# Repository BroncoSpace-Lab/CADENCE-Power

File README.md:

This repository contains the development of the Solar and Battery Management system Boards that will be used for the CADENCE mission.

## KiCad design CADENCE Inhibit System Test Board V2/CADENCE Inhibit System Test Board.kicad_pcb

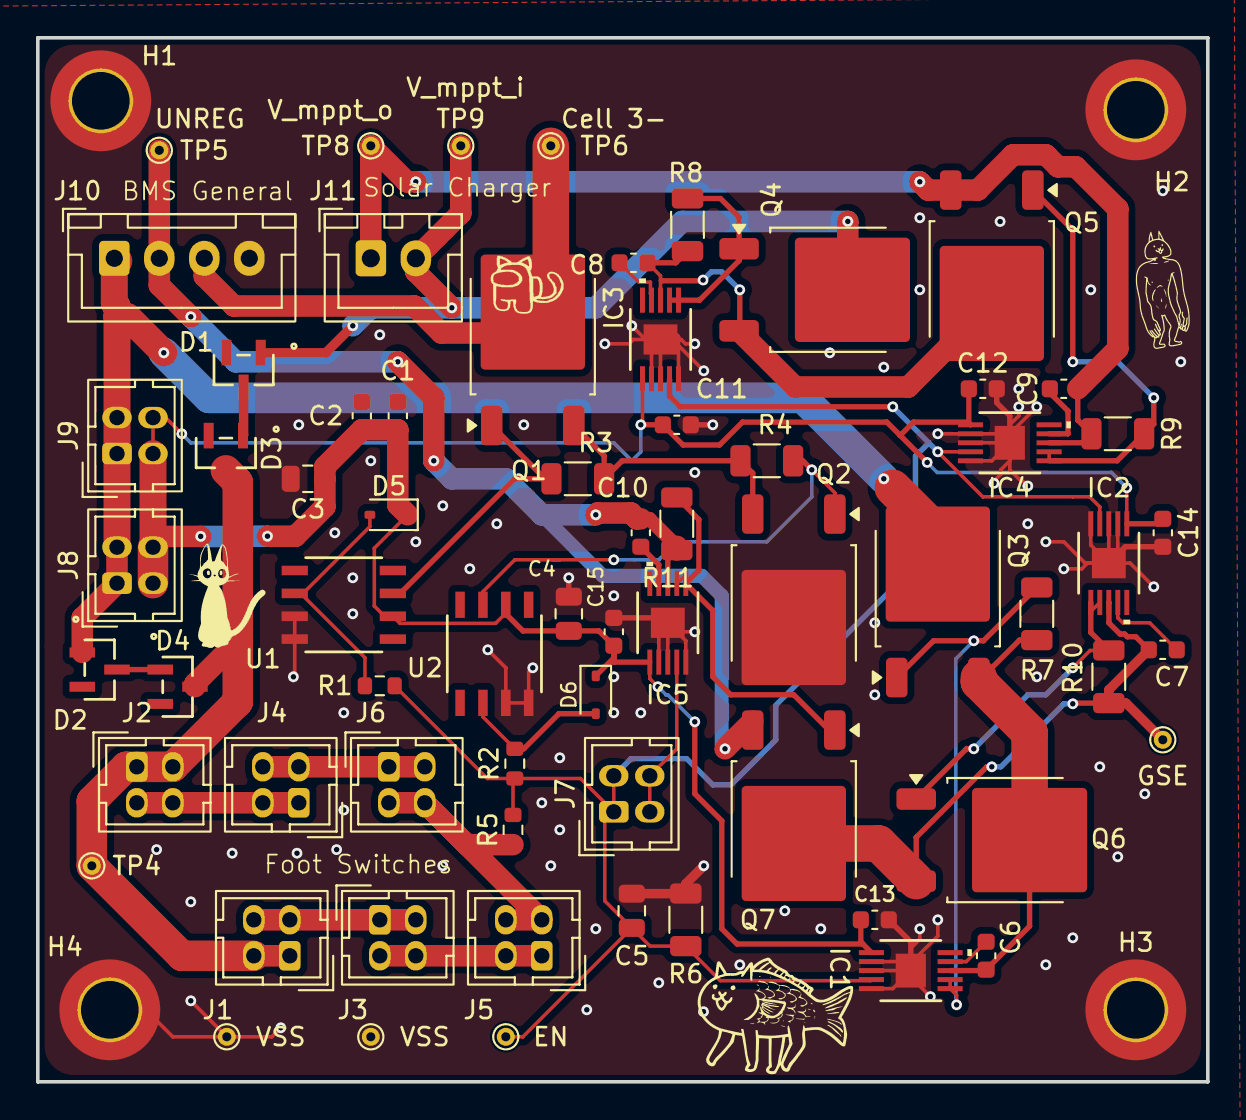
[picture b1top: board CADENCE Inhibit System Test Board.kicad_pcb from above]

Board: 2 copper layers, 65.0 x 58.0 mm, 70 parts (0 on the bottom side), 35 nets.

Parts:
C1, C2, C6, C7, C8, C9, C10, C11, C12, C13, C14, C15: 100nF; C_0603_1608Metric
C3, C4: 4.7uF; C_0805_2012Metric
C5: 10nF; C_0805_2012Metric
D1, D2, D3, D4: MMBD914LT1G; SOT-23_ONS
D5, D6: 1N5711WS-7-F; D_SOD-323
GSE: GSE; TestPoint_THTPad_D1.0mm_Drill0.5mm
H1, H2, H3, H4: MountingHole_Pad; MountingHole_3.2mm_M3_DIN965_Pad_TopOnly
IC1, IC2, IC3, IC4, IC5: LTC7004IMSE#WTRPBF; MSE_05-08-1664_ADI
J1, J2, J3, J4, J5, J6, J7, J8, J9: INHIBIT_P2; Hirose_DF11-4DP-2DSA_2x02_P2.00mm_Vertical
J10: Conn_01x04; JST_XH_B4B-XH-A_1x04_P2.50mm_Vertical
J11: Conn_01x02; JST_XH_B2B-XH-A_1x02_P2.50mm_Vertical
Q1, Q2, Q3, Q4, Q5, Q6, Q7: SUD23N06-31-GE3; TO-252-2
R1, R2: 47k; R_0603_1608Metric
R3, R4, R6, R7, R8, R9, R10, R11: 100K; R_1206_3216Metric
R5: 39k; R_0603_1608Metric
TP1, TP7: VSS; TestPoint_THTPad_D1.0mm_Drill0.5mm
TP2: EN; TestPoint_THTPad_D1.0mm_Drill0.5mm
TP4: Voltage Level; TestPoint_THTPad_D1.0mm_Drill0.5mm
TP5: UNREG; TestPoint_THTPad_D1.0mm_Drill0.5mm
TP6: Cell 3-; TestPoint_THTPad_D1.0mm_Drill0.5mm
TP8: V_mppt_o; TestPoint_THTPad_D1.0mm_Drill0.5mm
TP9: V_mppt_i; TestPoint_THTPad_D1.0mm_Drill0.5mm
U1, U2: MIC4427YM-TR; SOIC-8_M_MCH

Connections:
Cell 1+: D2.1 (A), J8.1, J8.3, J9.1, J9.3, J10.1, Q3.2 (D)
Cell 3-: J10.3, Q1.2 (D), TP6.1 (1_1)
EN: C5.2, IC1.4 (INP), IC2.4 (INP), IC3.4 (INP), IC4.4 (INP), J7.1, J7.3, R1.1, R2.1, R5.2, R6.1, TP2.1 (1_1)
HIGH_SIDE_PWR: C1.1, C2.1, C3.1, C4.1, C11.1, C12.1, C13.1, C14.1, C15.1, D5.1 (K), D6.1 (K), IC1.1 (VCC), IC2.1 (VCC), IC3.1 (VCC), IC4.1 (VCC), IC5.1 (VCC), J8.2, J8.4, J9.2, J9.4, U1.6 (V_{S}), U2.6 (V_{S})
unnamed: D1.3 (K), D3.1 (A)
unnamed: D2.3 (K), D4.1 (A)
unnamed: D3.3 (K), D4.3 (K), J1.1, J1.3, J2.1, J2.3, TP4.1 (1_1)
unnamed: D5.2 (A), R1.2, U1.2 (INA)
unnamed: D6.2 (A), R2.2, U2.2 (INA)
unnamed: C6.2, IC1.9 (BST)
unnamed: IC1.6 (TGDN), IC1.7 (TGUP), Q3.1 (G), R7.2
unnamed: C6.1, IC1.8 (TS), Q3.3 (S), Q6.2 (D), R7.1
unnamed: C7.2, IC2.9 (BST)
unnamed: IC2.6 (TGDN), IC2.7 (TGUP), Q6.1 (G), R10.2
unnamed: C7.1, GSE.1 (1_1), IC2.8 (TS), Q6.3 (S), Q7.2 (D), R10.1
unnamed: C8.2, IC3.9 (BST)
unnamed: IC3.6 (TGDN), IC3.7 (TGUP), Q4.1 (G), R8.2
unnamed: C8.1, IC3.8 (TS), Q4.3 (S), Q5.2 (D), R8.1
unnamed: C9.2, IC4.9 (BST)
unnamed: IC4.6 (TGDN), IC4.7 (TGUP), Q5.1 (G), R9.2
unnamed: C10.2, IC5.9 (BST)
unnamed: IC5.4 (INP), J7.2, J7.4
unnamed: IC5.6 (TGDN), IC5.7 (TGUP), Q7.1 (G), R11.2
unnamed: J1.2, J1.4, J3.1, J3.3
unnamed: J2.2, J2.4, J4.1, J4.3
unnamed: J3.2, J3.4, J5.1, J5.3
unnamed: J4.2, J4.4, J6.1, J6.3
unnamed: J5.2, J5.4, J6.2, J6.4, R5.1
unnamed: Q1.1 (G), R3.2, U1.7 (OUTA)
unnamed: Q1.3 (S), Q2.3 (S), R3.1, R4.2
unnamed: Q2.1 (G), R4.1, U2.7 (OUTA)
UNREG: C10.1, IC5.8 (TS), J10.2, Q7.3 (S), R11.1, TP5.1 (1_1)
VSS: C1.2, C2.2, C3.2, C4.2, C5.1, C11.2, C12.2, C13.2, C14.2, C15.2, H1.1 (1_1), H2.1 (1_1), H3.1 (1_1), H4.1 (1_1), IC1.2 (VCCUV), IC1.3 (GND_1), IC1.5 (OVLO), IC1.11 (GND_2), IC2.2 (VCCUV), IC2.3 (GND_1), IC2.5 (OVLO), IC2.11 (GND_2), IC3.2 (VCCUV), IC3.3 (GND_1), IC3.5 (OVLO), IC3.11 (GND_2), IC4.2 (VCCUV), IC4.3 (GND_1), IC4.5 (OVLO), IC4.11 (GND_2), IC5.2 (VCCUV), IC5.3 (GND_1), IC5.5 (OVLO), IC5.11 (GND_2), J10.4, Q2.2 (D), R6.2, TP1.1 (1_1), TP7.1 (1_1), U1.3 (GND), U1.4 (INB), U2.3 (GND), U2.4 (INB)
V_mppt_i: D1.1 (A), J11.2, Q4.2 (D), TP9.1 (1_1)
V_mppt_o: C9.1, IC4.8 (TS), J11.1, Q5.3 (S), R9.1, TP8.1 (1_1)

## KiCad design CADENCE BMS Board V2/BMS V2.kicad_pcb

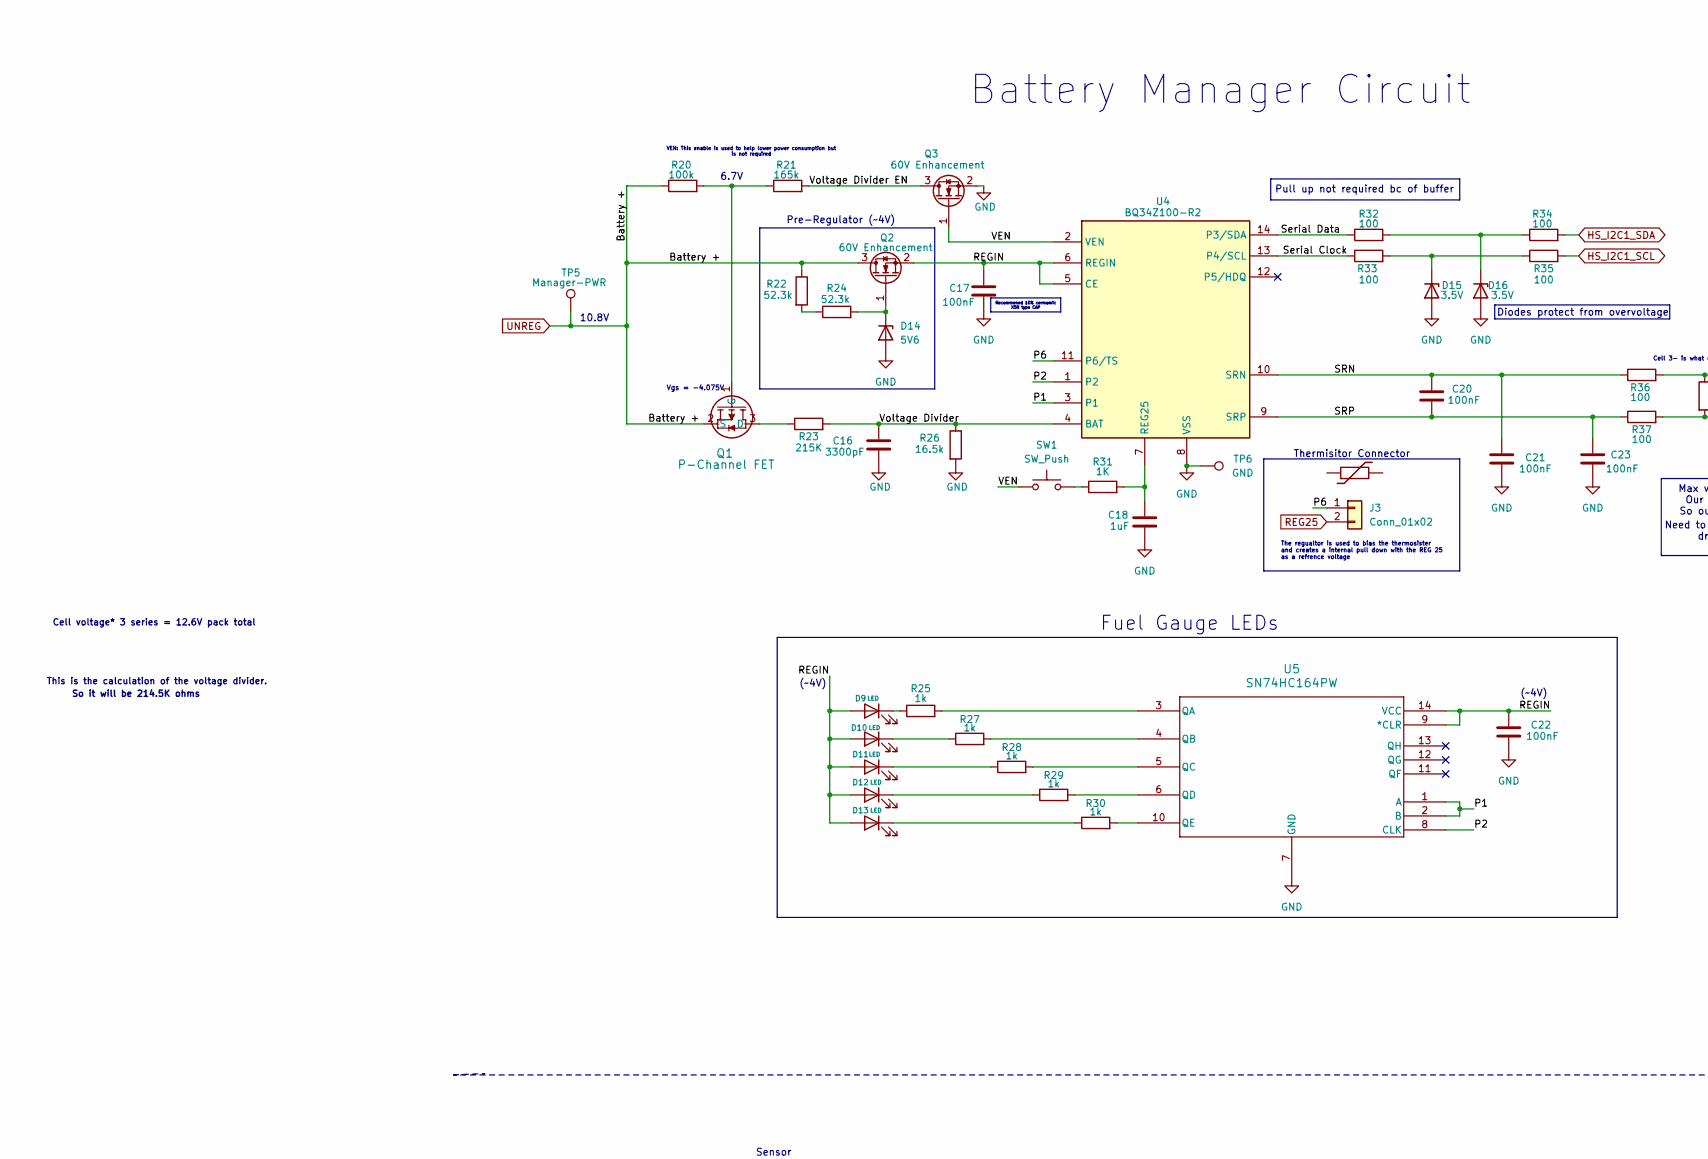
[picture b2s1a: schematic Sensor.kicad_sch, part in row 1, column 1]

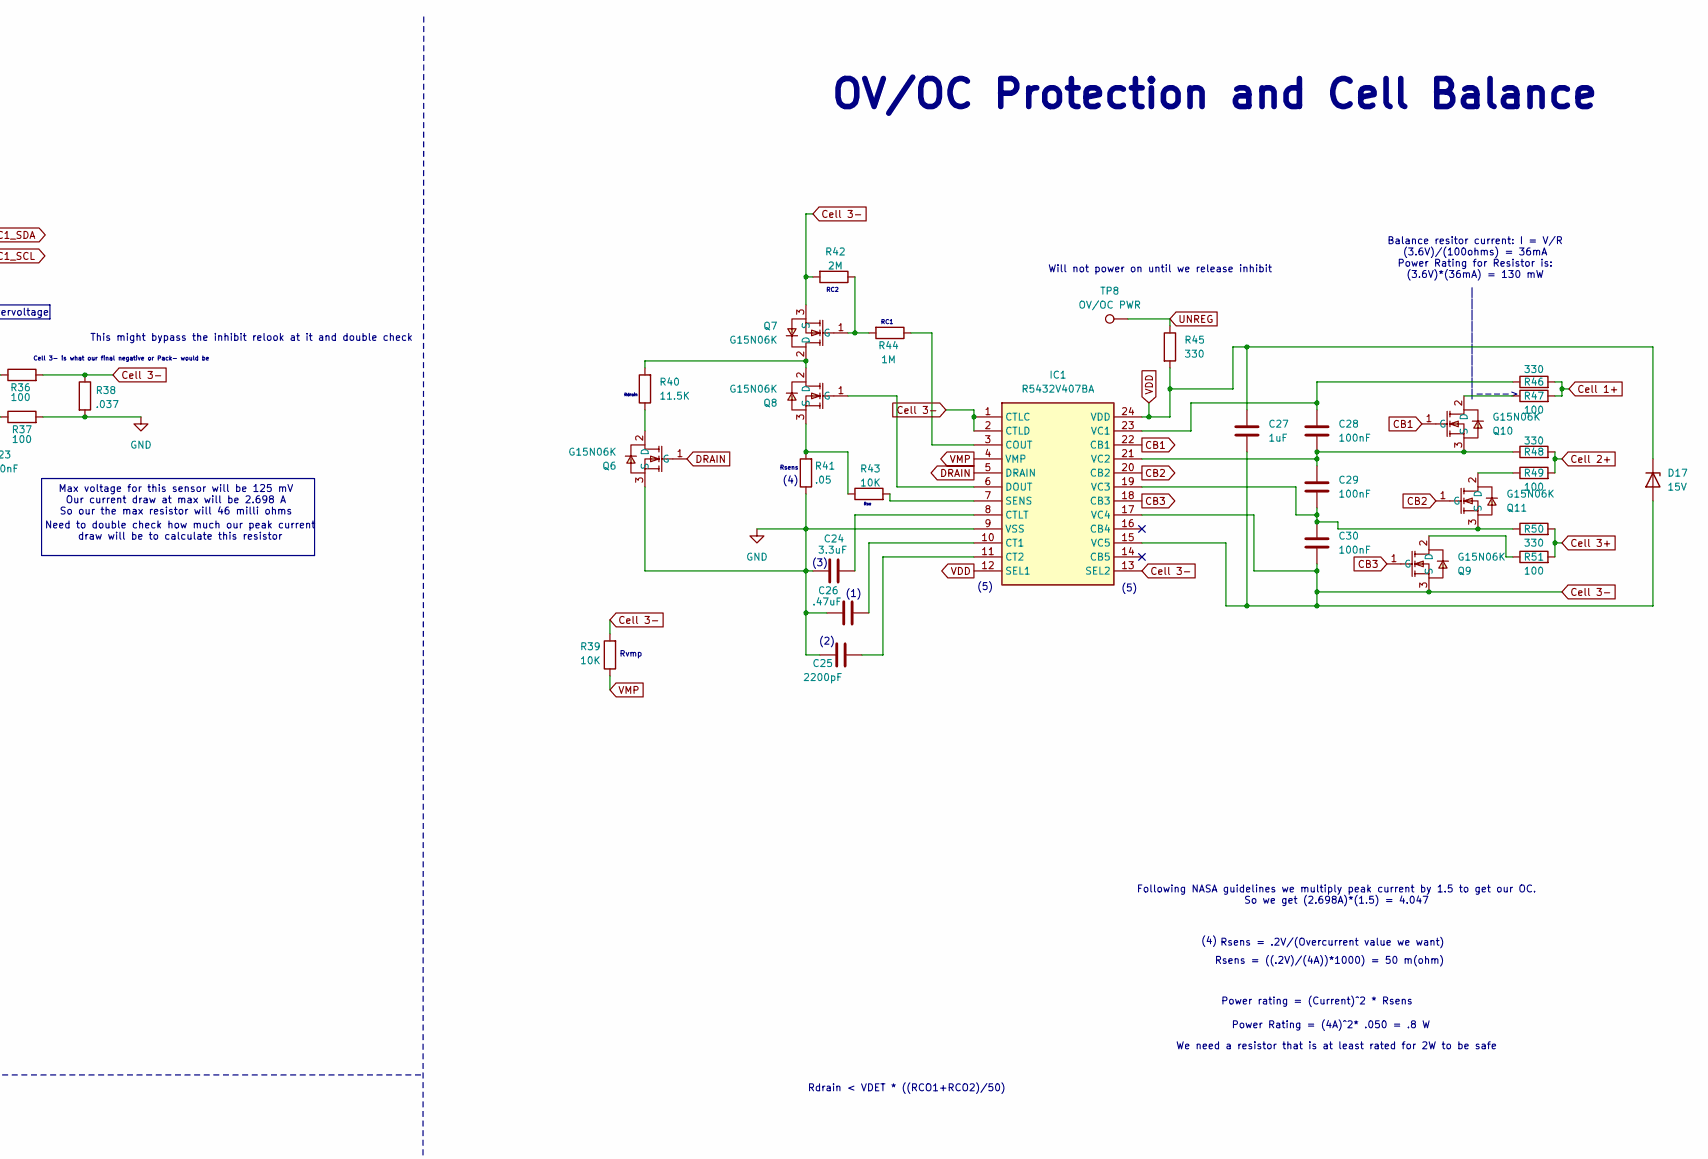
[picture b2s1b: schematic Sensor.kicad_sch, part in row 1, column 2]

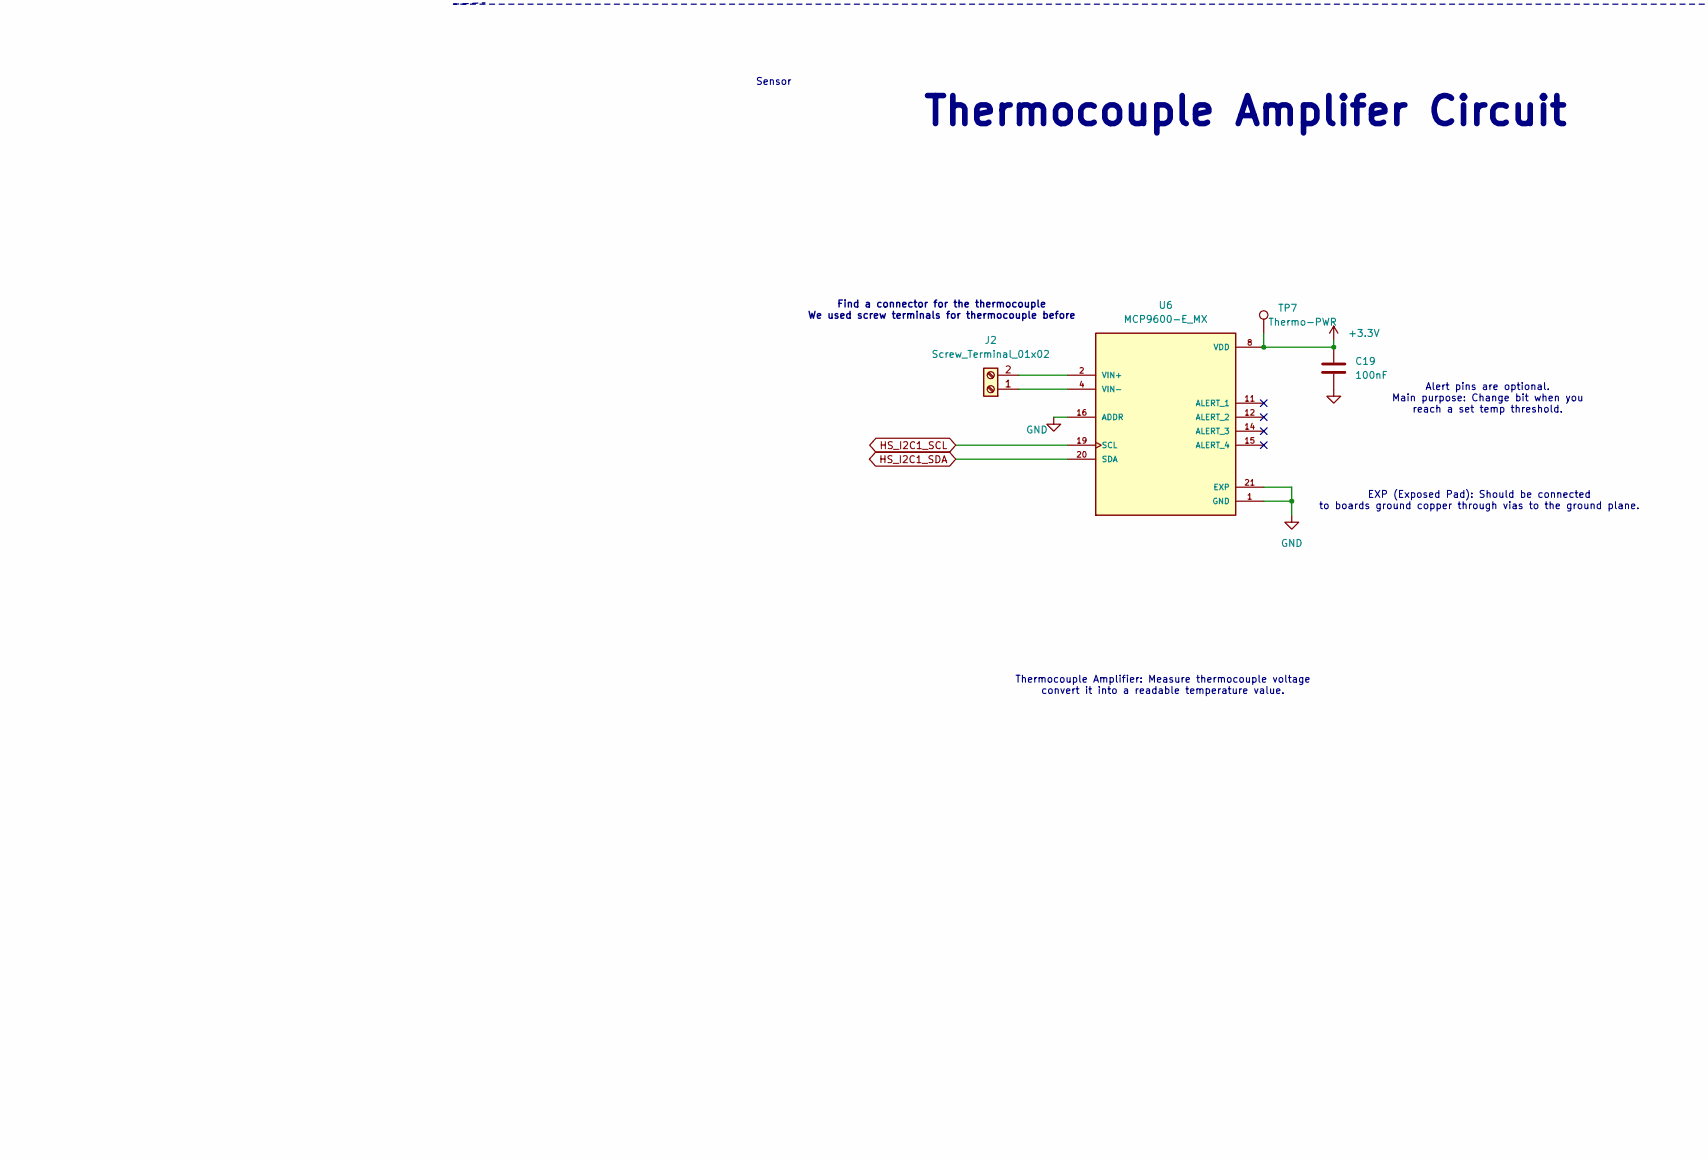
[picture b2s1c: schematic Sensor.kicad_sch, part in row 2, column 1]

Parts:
C16: 3300pF; C_0603_1608Metric
C17, C19, C20, C21, C23, C28, C29, C30: 100nF; C_0402_1005Metric
C18, C27: 1uF; C_0805_2012Metric
C22: 100nF; C_0805_2012Metric
C24: 3.3uF; C_0805_2012Metric
C25: 2200pF; C_0805_2012Metric
C26: .47uF; C_0805_2012Metric
D9, D10, D11, D12, D13: LED
D14: 5V6; D_SMA
D15, D16: 3.5V; D_SOD-123
D17: 15V; D_SOD-123
IC1: R5432V407BA; SOP65P760X140-24N; Manufacturer_Part_Number R5432V407BA
J2: Screw_Terminal_01x02; TerminalBlock_MaiXu_MX126-5.0-02P_1x02_P5.00mm
J3: Conn_01x02; JST_GH_SM02B-GHS-TB_1x02-1MP_P1.25mm_Horizontal
Q1: P-Channel FET; SOT-23-3
Q2, Q3: 60V Enhancement; SOT_N06-31-GE3_VIS
Q6, Q7, Q8, Q9, Q10, Q11: G15N06K; TO-252-2_L6.6-W6.2-P4.57-LS10.1-BR-CW; MPN G15N06K; LCSC Part C3038563
R20: 100k; R_1206_3216Metric
R21: 165k; R_1206_3216Metric
R22, R24: 52.3k; R_1206_3216Metric
R23: 215K; R_1206_3216Metric
R25, R27, R28, R29, R30: 1k
R26: 16.5k; R_1210_3225Metric
R31: 1K
R32, R33, R34, R35, R36, R37: 100; R_1206_3216Metric
R38: .037; R_2512_6332Metric
R39, R43: 10K; R_0603_1608Metric
R40: 11.5K; R_1206_3216Metric
R41: .05; STA_CSSH2728_STP
R42: 2M; R_0603_1608Metric
R44: 1M; R_2512_6332Metric
R45, R46, R48, R50: 330; R_0805_2012Metric
R47, R49, R51: 100; R_0402_1005Metric
SW1: SW_Push
TH2: Thermistor
TP5: Manager-PWR; TestPoint_THTPad_D1.0mm_Drill0.5mm
TP6: GND; TestPoint_THTPad_D1.0mm_Drill0.5mm
TP7: Thermo-PWR; TestPoint_THTPad_D1.0mm_Drill0.5mm
TP8: OV/OC PWR; TestPoint_THTPad_D1.0mm_Drill0.5mm
U4: BQ34Z100-R2; PW14_TEX; Manufacturer_Part_Number BQ34Z100-R2
U5: SN74HC164PW
U6: MCP9600-E_MX; MQFN20_NU_MCH; PARTREV F; DigiKey_Part_Number MCP96RL00-E/MX-ND

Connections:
+3.3V: C19.2, TP7.1 (1_1), U6.8 (VDD); also elsewhere on the board
/Sensors/P1: U4.3 (P1), U5.1 (A), U5.2 (B)
/Sensors/P2: U4.1 (P2), U5.8 (CLK)
/Sensors/P6: J3.1, U4.11 (P6/TS)
/Sensors/REGIN: C17.1, C22.2, D9.2 (A), D10.2 (A), D11.2 (A), D12.2 (A), D13.2 (A), Q2.2 (S), U4.5 (CE), U4.6 (REGIN), U5.9 (*CLR), U5.14 (VCC)
/Sensors/SRN: C20.1, C21.2, R36.1, U4.10 (SRN)
/Sensors/SRP: C20.2, C23.2, R37.1, U4.9 (SRP)
/Sensors/Serial Clock: R33.1, U4.13 (P4/SCL)
/Sensors/Serial Data: R32.1, U4.14 (P3/SDA)
/Sensors/VEN: Q3.1 (G), SW1.1, U4.2 (VEN)
/Sensors/Voltage Divider: C16.2, R23.2, R26.1, U4.4 (BAT)
/Sensors/Voltage Divider EN: Q3.3 (D), R21.2
CB1: IC1.22 (CB1), Q10.1 (G)
CB2: IC1.20 (CB2), Q11.1 (G)
CB3: IC1.18 (CB3), Q9.1 (G)
Cell 1+: R46.2, R47.2; also elsewhere on the board
Cell 2+: R48.2, R49.2; also elsewhere on the board
Cell 3+: R50.2, R51.2; also elsewhere on the board
Cell 3-: C27.2, C30.2, D17.2 (A), IC1.1 (CTLC), IC1.2 (CTLD), IC1.13 (SEL2), IC1.15 (VC5), IC1.17 (VC4), Q7.3 (S), Q9.3 (S), R36.2, R38.1, R39.2, R42.2; also elsewhere on the board
DRAIN: IC1.5 (DRAIN), Q6.1 (G)
HS_I2C1_SCL: R35.2, U6.19 (SCL); also elsewhere on the board
HS_I2C1_SDA: R34.2, U6.20 (SDA); also elsewhere on the board
unnamed: D9.1 (K), R25.1
unnamed: D10.1 (K), R27.1
unnamed: D11.1 (K), R28.1
unnamed: D12.1 (K), R29.1
unnamed: D13.1 (K), R30.1
unnamed: D14.1 (K), Q2.1 (G), R24.2
unnamed: D15.1 (K), R33.2, R35.1
unnamed: D16.1 (K), R32.2, R34.1
unnamed: IC1.3 (COUT), R44.1
unnamed: C26.2, IC1.10 (CT1)
unnamed: C25.1, IC1.11 (CT2)
unnamed: C24.2, IC1.8 (CTLT)
unnamed: IC1.6 (DOUT), Q8.1 (G)
unnamed: IC1.7 (SENS), R43.2
unnamed: C28.1, IC1.23 (VC1), R46.1
unnamed: C28.2, C29.1, IC1.21 (VC2), Q10.3 (S), R48.1
unnamed: C29.2, C30.1, IC1.19 (VC3), Q11.3 (S), R50.1
unnamed: J2.1, U6.4 (VIN-)
unnamed: J2.2, U6.2 (VIN+)
unnamed: Q1.3 (D), R23.1
unnamed: Q1.1 (G), R20.2, R21.1
unnamed: Q6.2 (D), R40.1
unnamed: Q7.2 (D), Q8.2 (D), R40.2
unnamed: Q7.1 (G), R42.1, R44.2
unnamed: Q8.3 (S), R41.2, R43.1
unnamed: Q9.2 (D), R51.1
unnamed: Q10.2 (D), R47.1
unnamed: Q11.2 (D), R49.1
unnamed: R22.2, R24.1
unnamed: R25.2, U5.3 (QA)
unnamed: R27.2, U5.4 (QB)
unnamed: R28.2, U5.5 (QC)
unnamed: R29.2, U5.6 (QD)
unnamed: R30.2, U5.10 (QE)
unnamed: R31.1, SW1.2
unnamed: C18.2, R31.2, U4.7 (REG25)
REG25: J3.2
Solar1-: C16.1, C17.2, C18.1, C19.1, C21.1, C22.1, C23.1, C24.1, C25.2, C26.1, D14.2 (A), D15.2 (A), D16.2 (A), IC1.9 (VSS), Q3.2 (S), Q6.3 (S), R26.2, R37.2, R38.2, R41.1, TP6.1 (1_1), U4.8 (VSS), U5.7 (GND), U6.1 (GND), U6.3 (GND), U6.5 (GND), U6.6 (GND), U6.7 (GND), U6.9 (GND), U6.10 (GND), U6.13 (GND), U6.16 (ADDR), U6.17 (GND), U6.18 (GND), U6.21 (EXP), U6.22 (EXP), U6.23 (EXP), U6.24 (EXP), U6.25 (EXP), U6.26 (EXP), U6.27 (EXP), U6.28 (EXP), U6.29 (EXP), U6.30 (EXP); also elsewhere on the board
UNREG: Q1.2 (S), Q2.3 (D), R20.1, R22.1, R45.1, TP5.1 (1_1), TP8.1 (1_1); also elsewhere on the board
VDD: C27.1, D17.1 (K), IC1.12 (SEL1), IC1.24 (VDD), R45.2
VMP: IC1.4 (VMP), R39.1

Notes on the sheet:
Rdrain < 12K
Will not power on until we release inhibit
Rvmp
(1)
This is the calculation of the voltage divider.
RC1
Diodes protect from overvoltage
Rsens
Recommened 10% cermamic X5R type CAP
(4)
Cell voltage* 3 series = 12.6V pack total
(2)
Balance resitor current: I = V/R (3.6V)/(100ohms) = 36mA Power Rating for Resistor is: (3.6V)*(36mA) = 130 mW
Fuel Gauge LEDs
OV/OC Protection and Cell Balance
Thermocouple Amplifier: Measure thermocouple voltage convert it into a readable temperature value.
Vgs = -4.075V
Sensor
Rdrain
(5)
Find a connector for the thermocouple We used screw terminals for thermocouple before
Alert pins are optional. Main purpose: Change bit when you reach a set temp threshold.
This might bypass the inhibit relook at it and double check
(3)
We will follow the datasheet for the values of RCO1 and RCO2
Rsens = .2V/(Overcurrent value we want)
Pull up not required bc of buffer
Power rating = (Current)^2 * Rsens
Rdrain < .2V *((1M + 2M)/50)
Battery Manager Circuit
Thermisitor Connector
The regualtor is used to bias the thermosister and creates a internal pull down with the REG 25 as a refrence voltage
(~4V)
Rsens = ((.2V)/(4A))*1000) = 50 m(ohm)
Need to double check how much our peak current draw will be to calculate this resistor
Following NASA guidelines we multiply peak current by 1.5 to get our OC. So we get (2.698A)*(1.5) = 4.047
I will be using 11.5K
We need a resistor that is at least rated for 2W to be safe
10.8V
RC2

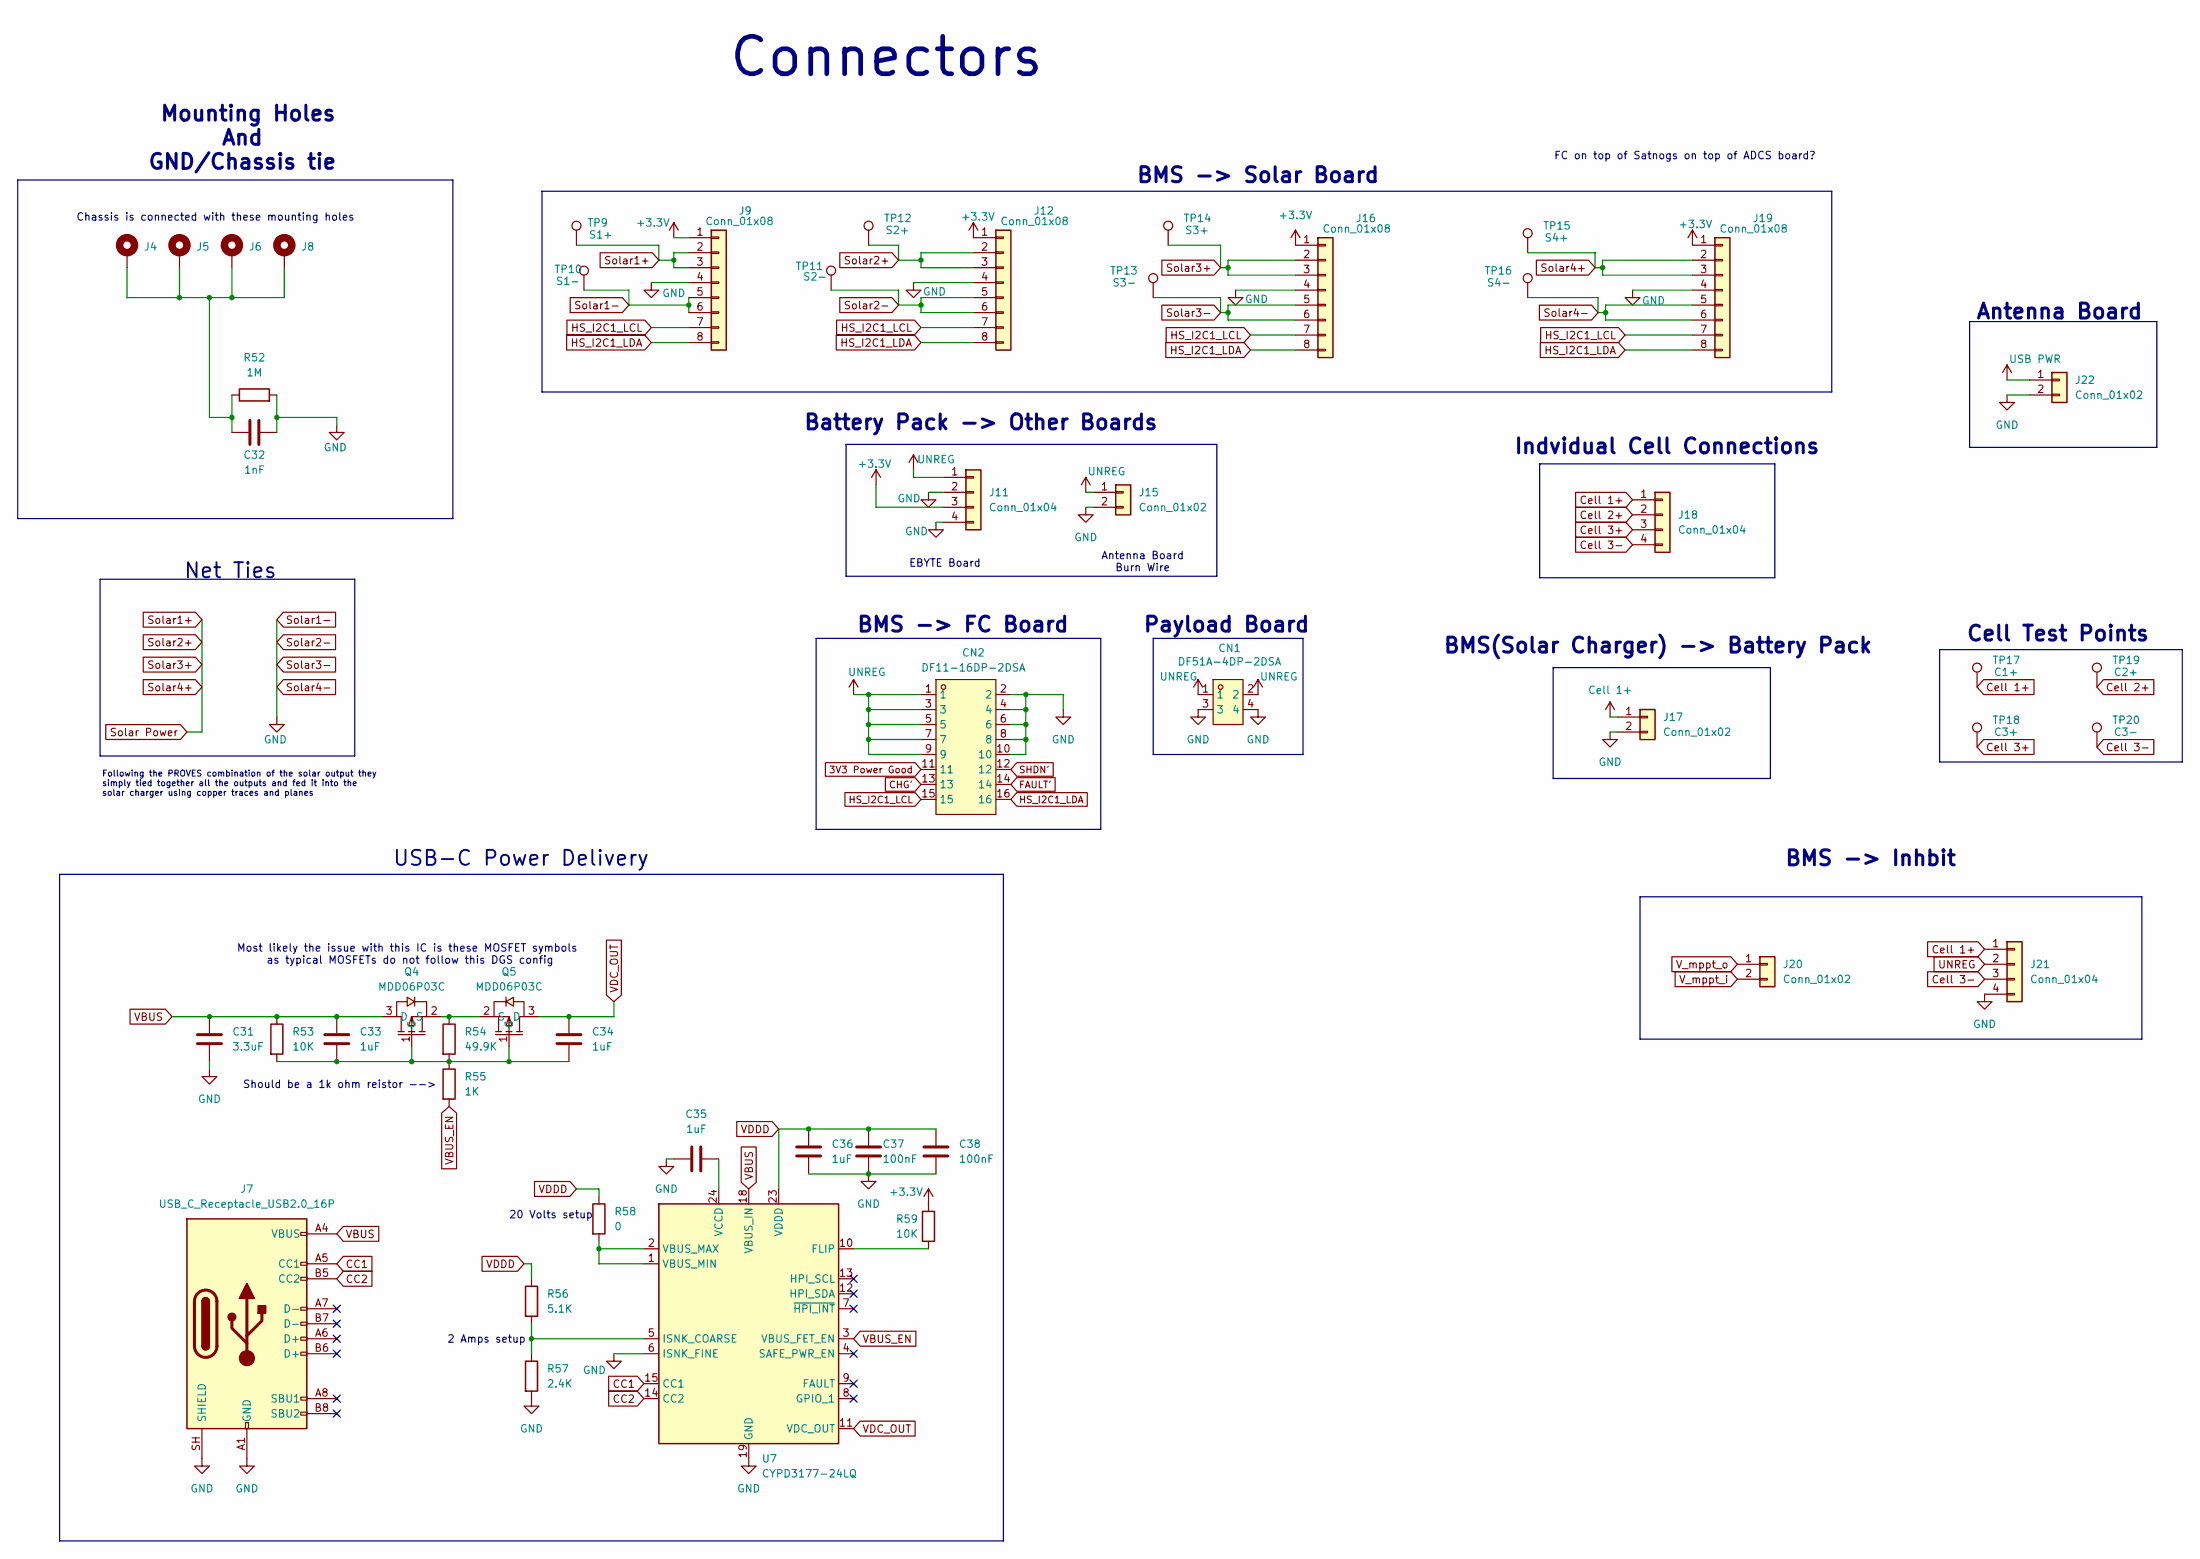
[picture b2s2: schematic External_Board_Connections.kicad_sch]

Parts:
C31: 3.3uF; C_0805_2012Metric
C32: 1nF; C_0805_2012Metric
C33, C34, C35, C36: 1uF; C_0805_2012Metric
C37, C38: 100nF; C_0603_1608Metric
CN1: DF51A-4DP-2DSA; CONN-TH_DF51A-4DP-2DSA; MPN DF51A-4DP-2DSA; LCSC Part C17407689
CN2: DF11-16DP-2DSA; CONN-TH_DF11-16DP-2DSA-08; MPN DF11-16DP-2DSA(08); LCSC Part C530981
J4, J5, J6, J8: Conn_01x01_Socket; MountingHole_3.2mm_M3_DIN965_Pad_TopOnly
J7: USB_C_Receptacle_USB2.0_16P; USB_C_Receptacle_HRO_TYPE-C-31-M-12
J9, J12, J16, J19: Conn_01x08; Hirose_DF11-8DP-2DSA_2x04_P2.00mm_Vertical
J11, J21: Conn_01x04; JST_XH_B4B-XH-A_1x04_P2.50mm_Vertical
J15, J17, J20: Conn_01x02; JST_XH_B2B-XH-A_1x02_P2.50mm_Vertical
J18: Conn_01x04; LC04T
J22: Conn_01x02; SHDR2W120P580X500_2X1_790X1380X1460P
Q4, Q5: MDD06P03C; SOT-23-3L_L2.9-W1.6-P1.90-LS2.8-BL; MPN MDD06P03C; LCSC Part C53069233
R52: 1M; R_2512_6332Metric
R53: 10K; R_0603_1608Metric_Pad0.98x0.95mm_HandSolder
R54: 49.9K; R_0603_1608Metric
R55: 1K; R_0603_1608Metric
R56: 5.1K; R_0603_1608Metric_Pad0.98x0.95mm_HandSolder
R57: 2.4K; R_0603_1608Metric
R58: 0; R_0603_1608Metric
R59: 10K; R_0603_1608Metric
TP9: S1+; TestPoint_THTPad_D1.0mm_Drill0.5mm
TP10: S1-; TestPoint_THTPad_D1.0mm_Drill0.5mm
TP11: S2-; TestPoint_THTPad_D1.0mm_Drill0.5mm
TP12: S2+; TestPoint_THTPad_D1.0mm_Drill0.5mm
TP13: S3-; TestPoint_THTPad_D1.0mm_Drill0.5mm
TP14: S3+; TestPoint_THTPad_D1.0mm_Drill0.5mm
TP15: S4+; TestPoint_THTPad_D1.0mm_Drill0.5mm
TP16: S4-; TestPoint_THTPad_D1.0mm_Drill0.5mm
TP17: C1+; TestPoint_THTPad_D1.0mm_Drill0.5mm
TP18: C3+; TestPoint_THTPad_D1.0mm_Drill0.5mm
TP19: C2+; TestPoint_THTPad_D1.0mm_Drill0.5mm
TP20: C3-; TestPoint_THTPad_D1.0mm_Drill0.5mm
U7: CYPD3177-24LQ; QFN-24-1EP_4x4mm_P0.5mm_EP2.75x2.75mm

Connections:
3V3 Power Good: CN2.11; also elsewhere on the board
+3.3V: J9.1, J11.3, J12.1, J16.1, J19.1, R59.1; also elsewhere on the board
CC1: J7.A5 (CC1), U7.15 (CC1)
CC2: J7.B5 (CC2), U7.14 (CC2)
CHG': CN2.13; also elsewhere on the board
Cell 1+: J17.1, J18.1, J21.1, TP17.1 (1_1); also elsewhere on the board
Cell 2+: J18.2, TP19.1 (1_1); also elsewhere on the board
Cell 3+: J18.3, TP18.1 (1_1); also elsewhere on the board
Cell 3-: J18.4, J21.3, TP20.1 (1_1); also elsewhere on the board
FAULT': CN2.14; also elsewhere on the board
HS_I2C1_LCL: CN2.15, J9.7, J12.7, J16.7, J19.7; also elsewhere on the board
HS_I2C1_LDA: CN2.16, J9.8, J12.8, J16.8, J19.8; also elsewhere on the board
unnamed: C32.1, J4.1 (1_1), J5.1 (1_1), J6.1 (1_1), J8.1 (1_1), R52.1
unnamed: C33.2, C34.2, Q4.1 (G), Q5.1 (G), R53.2, R54.2, R55.1
unnamed: Q4.2 (S), Q5.2 (S), R54.1
unnamed: R59.2, U7.10 (FLIP)
unnamed: R56.2, R57.1, U7.5 (ISNK_COARSE)
unnamed: R58.2, U7.1 (VBUS_MIN), U7.2 (VBUS_MAX)
unnamed: C35.2, U7.24 (VCCD)
SHDN': CN2.12; also elsewhere on the board
Solar1-: C31.2, C32.2, C35.1, C36.2, C37.2, C38.2, CN1.3, CN1.4, CN2.2, CN2.4, CN2.6, CN2.8, CN2.10, J7.A1 (GND), J7.A12 (GND), J7.B1 (GND), J7.B12 (GND), J7.SH (SHIELD), J9.4, J9.5, J9.6, J11.2, J11.4, J12.4, J12.5, J12.6, J15.2, J16.4, J16.5, J16.6, J17.2, J19.4, J19.5, J19.6, J21.4, J22.2, R52.2, R57.2, TP10.1 (1_1), TP11.1 (1_1), TP13.1 (1_1), TP16.1 (1_1), U7.6 (ISNK_FINE), U7.19 (GND), U7.22 (GND), U7.25 (GND); also elsewhere on the board
Solar Power: J9.2, J9.3, J12.2, J12.3, J16.2, J16.3, J19.2, J19.3, TP9.1 (1_1), TP12.1 (1_1), TP14.1 (1_1), TP15.1 (1_1); also elsewhere on the board
UNREG: CN1.1, CN1.2, CN2.1, CN2.3, CN2.5, CN2.7, CN2.9, J11.1, J15.1, J21.2; also elsewhere on the board
USB PWR: J22.1
VBUS: C31.1, C33.1, J7.A4 (VBUS), J7.A9 (VBUS), J7.B4 (VBUS), J7.B9 (VBUS), Q4.3 (D), R53.1, U7.18 (VBUS_IN)
VBUS_EN: R55.2, U7.3 (VBUS_FET_EN)
VDC_OUT: C34.1, Q5.3 (D), U7.11 (VDC_OUT); also elsewhere on the board
VDDD: C36.1, C37.1, C38.1, R56.1, R58.1, U7.23 (VDDD)
V_mppt_i: J20.2; also elsewhere on the board
V_mppt_o: J20.1; also elsewhere on the board

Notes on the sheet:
Mounting Holes And GND/Chassis tie
2 Amps setup
EBYTE Board
Cell Test Points
Antenna Board
Antenna Board Burn Wire
Most likely the issue with this IC is these MOSFET symbols as typical MOSFETs do not follow this DGS config
20 Volts setup
FC on top of Satnogs on top of ADCS board?
Following the PROVES combination of the solar output they simply tied together all the outputs and fed it into the solar charger using copper traces and planes
Chassis is connected with these mounting holes
BMS -> Inhbit
Payload Board
Indvidual Cell Connections
Battery Pack -> Other Boards
BMS(Solar Charger) -> Battery Pack
Net Ties
Connectors
BMS -> FC Board
BMS -> Solar Board
Should be a 1k ohm reistor -->
USB-C Power Delivery
